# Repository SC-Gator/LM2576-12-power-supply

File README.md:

# LM2576-12 based power supply

A simple DIY switching power supply for Eurorack modular synths. This is an attempt to offer a high power but very cheap option for DIY synth makers.

Requires 15V DC input, recommended 3A. You could use a slighty higher voltage but efficiency will decrease. You can decrease input power, if you think you'll use less than the max rating. Use higher power at your own risk!

Have not been able to test the output power, but could be about: +12V/2000mA, -12V/600mA, 5V/300mA. Could vary a lot, especially as 5V regulator takes power from 12V line. Maybe a future redesign will take power from the input line. Be careful to use components (like the inductors) that can support the load.

It is based on the LM2576-12 component, which is a fixed voltage switching step-down voltage regulator. Switching power supplies are supposedly not suitable for audio but I decided to try it because many people use them in their synths, with models like the MeanWell RT-65B, with decent results. In my limited testing, there is no audible noise, and the AC setting on a 4000 count multimeter shows 0 millivolts.

I would be very grateful if someone with a oscilloscope tested this, and could give me feedback on ripple and spikes.

Possible future plans are to make a panel mount module version, an SMT version, and an adjustable output version. Possibly all in one.

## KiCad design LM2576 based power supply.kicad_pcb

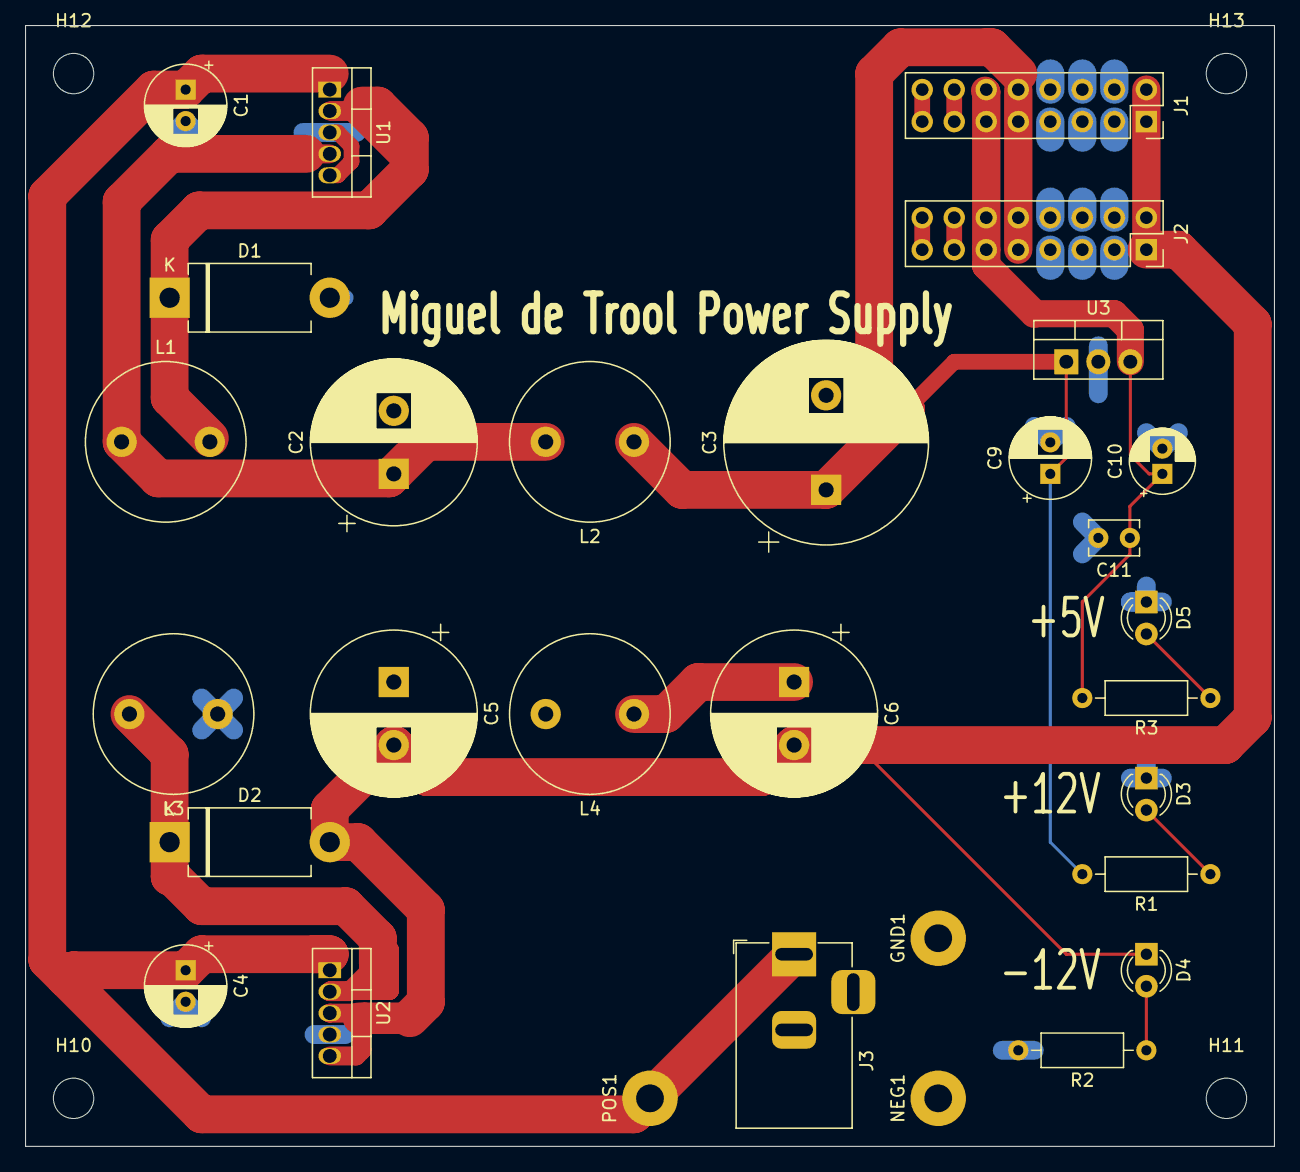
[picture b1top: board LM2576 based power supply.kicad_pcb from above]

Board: 2 copper layers, 99.1 x 88.9 mm, 34 parts (0 on the bottom side), 16 nets.

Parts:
C1, C4: 100µF; CP_Radial_D6.3mm_P2.50mm
C2, C5, C6: 2200µF; CP_Radial_D13.0mm_P5.00mm
C3: 4700µF; CP_Radial_D16.0mm_P7.50mm
C9: 100µf; CP_Radial_D6.3mm_P2.50mm
C10: 10µF; CP_Radial_D5.0mm_P2.00mm
C11: 100nF; C_Disc_D3.8mm_W2.6mm_P2.50mm
D1, D2: 1N5822; D_DO-201AD_P12.70mm_Horizontal
D3, D4, D5: LED; LED_D3.0mm
GND1: MountingHole_Pad real ground; MountingHole_2.2mm_M2_Pad
H10, H11, H12, H13: MountingHole; MountingHole_3.2mm_M3
J1, J2: Conn_02x08_Odd_Even; PinSocket_2x08_P2.54mm_Vertical
J3: Barrel_Jack; BarrelJack_Horizontal
L1, L2, L3, L4: 100µH; L_Radial_D12.5mm_P7.00mm_Fastron_09HCP
NEG1: MountingHole_Pad; MountingHole_2.2mm_M2_Pad
POS1: MountingHole_Pad; MountingHole_2.2mm_M2_Pad
R1, R2, R3: 1000; R_Axial_DIN0207_L6.3mm_D2.5mm_P10.16mm_Horizontal
U1, U2: LM2576T-12; TO-220-5_Vertical
U3: LM7805_TO220; TO-220-3_Vertical

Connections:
+15V: C1.1, C4.1, J3.1, POS1.1, U1.1, U2.1
GND: C1.2, C2.2, C3.2, C4.2, C5.1, C9.2, C10.2, C11.2, D1.2, D3.1, D5.1, GND1.1, J1.3, J1.4, J1.5, J1.6, J1.7, J1.8, J2.3, J2.4, J2.5, J2.6, J2.7, J2.8, J3.2, L3.1, L4.2, NEG1.1, R2.2, U1.3, U1.5, U2.4, U3.2
unnamed: C2.1, L1.1, L2.2, U1.4
unnamed: C3.1, C9.1, J1.9, J1.10, J2.9, J2.10, L2.1, R1.2, U3.1
unnamed: C5.2, C6.2, D2.2, D4.1, J1.1, J1.2, J2.1, J2.2, U2.3, U2.5
unnamed: C6.1, L4.1
unnamed: C10.1, C11.1, J1.11, J1.12, J2.11, J2.12, R3.2, U3.3
unnamed: D1.1, L1.2, U1.2
unnamed: D2.1, L3.2, U2.2
unnamed: D3.2, R1.1
unnamed: D4.2, R2.1
unnamed: D5.2, R3.1
unnamed: J1.13, J1.14
unnamed: J1.15, J1.16
unnamed: J2.13, J2.14
unnamed: J2.15, J2.16

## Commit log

2020-11-13 Create LICENSE
